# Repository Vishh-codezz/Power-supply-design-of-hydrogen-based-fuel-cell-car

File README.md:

# Power-supply-design-of-hydrogen-based-fuel-cell-car
I have developed nine power supply designs of on board battery and fuel cell battery. On board battery supply: 24V to 3.3V, 5V, 12V, dual 12V, dual 5V . Fuel cell supply: 48V to 3.3V, 5V, 12V, dual 5V, dual 12V.

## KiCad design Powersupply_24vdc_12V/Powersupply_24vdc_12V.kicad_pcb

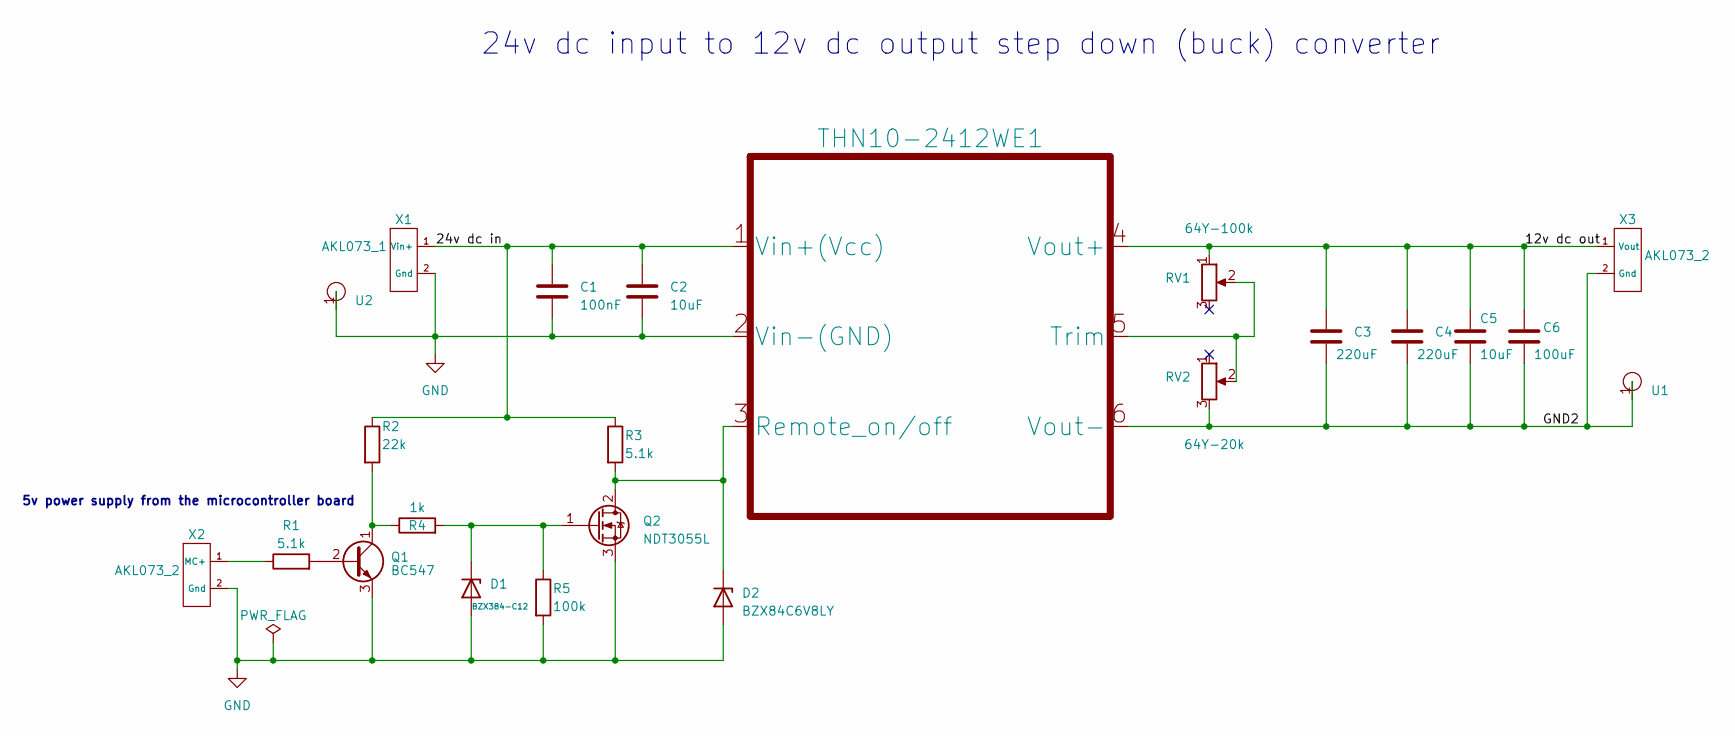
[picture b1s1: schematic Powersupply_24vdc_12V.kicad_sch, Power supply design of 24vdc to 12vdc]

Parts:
C1: 100nF; C_0603_1608Metric_Pad1.08x0.95mm_HandSolder
C2, C5: 10uF; C_1210_3225Metric_Pad1.33x2.70mm_HandSolder
C3, C4: 220uF
C6: 100uF; C_0603_1608Metric_Pad1.08x0.95mm_HandSolder
D1: BZX384-C12; BZX384_C12
D2: BZX84C6V8LY; BZX84C6V8
Q1: BC547; TO-92_Inline
Q2: NDT3055L; SOT-223-3_TabPin2
R1, R3: 5.1k; R_0603_1608Metric_Pad0.98x0.95mm_HandSolder
R2: 22k; R_0603_1608Metric_Pad0.98x0.95mm_HandSolder
R4: 1k; R_0603_1608Metric_Pad0.98x0.95mm_HandSolder
R5: 100k; R_1206_3216Metric_Pad1.30x1.75mm_HandSolder
RV1: 64Y-100k; Trim_potentiometer
RV2: 64Y-20k; 64Y-20k_potentiometer
THN10-2412WE1: Traco_THN-2412WE
U1, U2: Soldernail
X1: AKL073_1; 2pin_screwterminal
X2, X3: AKL073_2; 2pin_screwterminal

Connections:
/12v dc out: C3.1, C4.1, C5.1, C6.1, RV1.1, THN10-2412WE1.4 (Vout+), X3.1 (Vout); also elsewhere on the board
/24v dc in: C1.1, C2.1, R2.1, R3.1, THN10-2412WE1.1 (Vin+(Vcc)), X1.1 (Vin+); also elsewhere on the board
/GND2: C3.2, C4.2, C5.2, C6.2, RV2.3, THN10-2412WE1.6 (Vout-), U1.1, X3.2 (Gnd); also elsewhere on the board
GND: C1.2, C2.2, D1.2 (A), D2.2 (A), Q1.3 (E), Q2.3 (S), R5.2, THN10-2412WE1.2 (Vin-(GND)), U2.1, X1.2 (Gnd), X2.2 (Gnd); also elsewhere on the board
unnamed: D1.1 (K), Q2.1 (G), R4.2, R5.1
unnamed 5: D2.1 (K), Q2.2 (D), R3.2, THN10-2412WE1.3 (Remote_on/off); also elsewhere on the board
unnamed: Q1.2 (B), R1.2
unnamed: Q1.1 (C), R2.2, R4.1
unnamed 8: RV1.2, RV2.2, THN10-2412WE1.5 (Trim); also elsewhere on the board
unnamed: R1.1, X2.1 (MC+)

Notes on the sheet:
24v dc input to 12v dc output step down (buck) converter
5v power supply from the microcontroller board

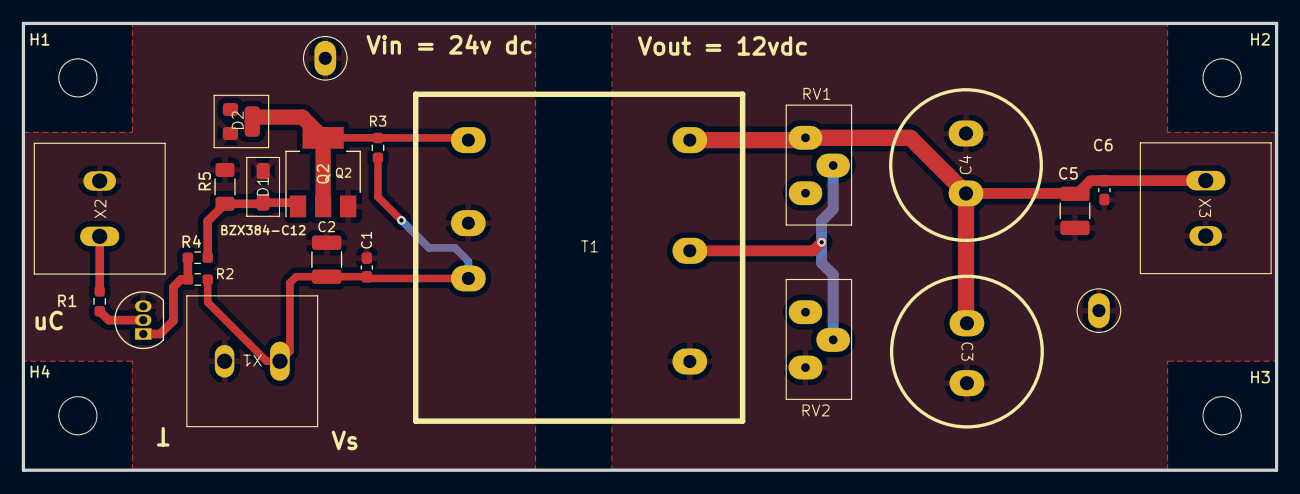
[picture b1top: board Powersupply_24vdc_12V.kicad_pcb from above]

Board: 2 copper layers, 115.0 x 41.0 mm, 27 parts (0 on the bottom side), 10 nets.

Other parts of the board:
H1, H2, H3, H4: MountingHole_3.5mm
T1: THN10-2412WE1; Traco_THN-2412WE

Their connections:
/12v dc out: T1.4 (Vout+); also elsewhere on the board
/24v dc in: T1.1 (Vin+(Vcc)); also elsewhere on the board
/GND2: T1.6 (Vout-); also elsewhere on the board
GND: T1.2 (Vin-(GND)); also elsewhere on the board
unnamed 5: T1.3 (Remote_on/off); also elsewhere on the board
unnamed 8: T1.5 (Trim); also elsewhere on the board

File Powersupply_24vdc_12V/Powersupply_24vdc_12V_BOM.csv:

Source:,C:\Kicad\Powersupply_12V\Powersupply_24vdc_12V\Powersupply_24vdc_12V.kicad_sch,,,,,,
Date:,6/11/2024 13:01,,,,,,
Tool:,Eeschema 7.0.1,,,,,,
Generator:,C:\Program Files\KiCad\7.0\bin\scripting\plugins/bom_csv_grouped_by_value_with_fp.py,,,,,,
Component Count:,23,,,,,,
Ref,Qnty,Value,Cmp name,Footprint,Description,Vendor,DNP
C1,1,100nF,C,Capacitor_SMD:C_0603_1608Metric_Pad1.08x0.95mm_HandSolder,Unpolarized capacitor,,
"C2, C5",2,10uF,C,Capacitor_SMD:C_1210_3225Metric_Pad1.33x2.70mm_HandSolder,Unpolarized capacitor,,
"C3, C4",2,220uF,C,220uf_capacitor:220uF,Unpolarized capacitor,,
C6,1,100uF,C,Capacitor_SMD:C_0603_1608Metric_Pad1.08x0.95mm_HandSolder,Unpolarized capacitor,,
D1,1,BZX384-C12,D_Zener,Zenerdiode_D1:BZX384_C12,Zener diode,,
D2,1,BZX84C6V8LY,D_Zener,Zenerdiode_D2:BZX84C6V8,Zener diode,,
Q1,1,BC547,BC547,Package_TO_SOT_THT:TO-92_Inline,"0.1A Ic, 45V Vce, Small Signal NPN Transistor, TO-92",,
Q2,1,NDT3055L,NDT3055L,Package_TO_SOT_SMD:SOT-223-3_TabPin2,"4A Id, 60V Vds, N-Channel Logic Level Enhancement Mode MOSFET, SOT-223",,
"R1, R3",2,5.1k,R,Resistor_SMD:R_0603_1608Metric_Pad0.98x0.95mm_HandSolder,Resistor,,
R2,1,22k,R,Resistor_SMD:R_0603_1608Metric_Pad0.98x0.95mm_HandSolder,Resistor,,
R4,1,1k,R,Resistor_SMD:R_0603_1608Metric_Pad0.98x0.95mm_HandSolder,Resistor,,
R5,1,100k,R,Resistor_SMD:R_1206_3216Metric_Pad1.30x1.75mm_HandSolder,Resistor,,
RV1,1,64Y-100k,R_Potentiometer,64Y-100k:Trim_potentiometer,Potentiometer,,
RV2,1,64Y-20k,R_Potentiometer,64Y-20k:64Y-20k_potentiometer,Potentiometer,,
THN10-2412WE1,1,~,THN10-2412WE,THN-2412WE:Traco_THN-2412WE,,,
"U1, U2",2,~,soldernail,soldernail-RTML:Soldernail,,,
X1,1,AKL073_1,input_1,AKL073_2:2pin_screwterminal,,,
"X2, X3",2,AKL073_2,input_2,AKL073_2:2pin_screwterminal,,,

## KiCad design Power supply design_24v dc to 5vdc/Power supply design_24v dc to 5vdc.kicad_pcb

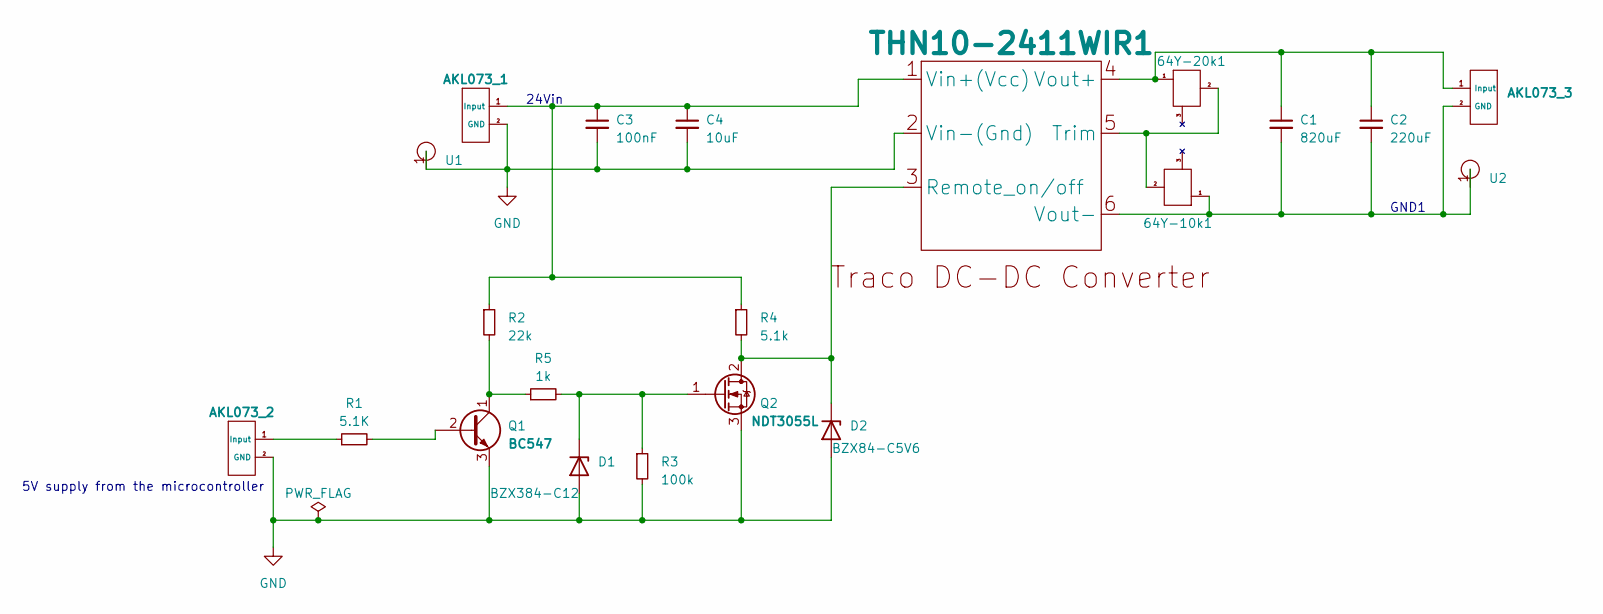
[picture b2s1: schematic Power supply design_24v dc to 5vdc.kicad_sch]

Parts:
64Y-10k1, 64Y-20k1: 64Y-100k
AKL073_1, AKL073_2, AKL073_3: Screw-terminal
C1: 820uF; 820uF_63V
C2: 220uF
C3: 100nF; C_1210_3225Metric_Pad1.33x2.70mm_HandSolder
C4: 10uF; C_1210_3225Metric_Pad1.33x2.70mm_HandSolder
D1: BZX384-C12; Zenerdiode_5.6V
D2: BZX84-C5V6
Q1: BC547; TO-92_Inline
Q2: NDT3055L; SOT-223-3_TabPin2
R1: 5.1K; R_0603_1608Metric_Pad0.98x0.95mm_HandSolder
R2: 22k; R_0603_1608Metric_Pad0.98x0.95mm_HandSolder
R3: 100k; R_1206_3216Metric_Pad1.30x1.75mm_HandSolder
R4: 5.1k; R_0603_1608Metric_Pad0.98x0.95mm_HandSolder
R5: 1k; R_0603_1608Metric_Pad0.98x0.95mm_HandSolder
THN10-2411WIR1: THN2411WIR
U1, U2: Soldernail

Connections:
GND: AKL073_1.2 (GND), AKL073_2.2 (GND), C3.2, C4.2, D1.2 (A), D2.2 (A), Q1.3 (E), Q2.3 (S), R3.2, THN10-2411WIR1.2 (Vin-(Gnd)), U1.1
unnamed: AKL073_1.1 (Input), C3.1, C4.1, R2.1, R4.1, THN10-2411WIR1.1 (Vin+(Vcc))
unnamed: AKL073_2.1 (Input), R1.1
unnamed: 64Y-10k1.1, AKL073_3.2 (GND), C1.2, C2.2, THN10-2411WIR1.6 (Vout-), U2.1
unnamed: 64Y-20k1.1, AKL073_3.1 (Input), C1.1, C2.1, THN10-2411WIR1.4 (Vout+)
unnamed: D1.1 (K), Q2.1 (G), R3.1, R5.2
unnamed: D2.1 (K), Q2.2 (D), R4.2, THN10-2411WIR1.3 (Remote_on/off)
unnamed: Q1.2 (B), R1.2
unnamed: Q1.1 (C), R2.2, R5.1
unnamed: 64Y-10k1.2, 64Y-20k1.2, THN10-2411WIR1.5 (Trim)

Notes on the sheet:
5V supply from the microcontroller
GND1
24Vin

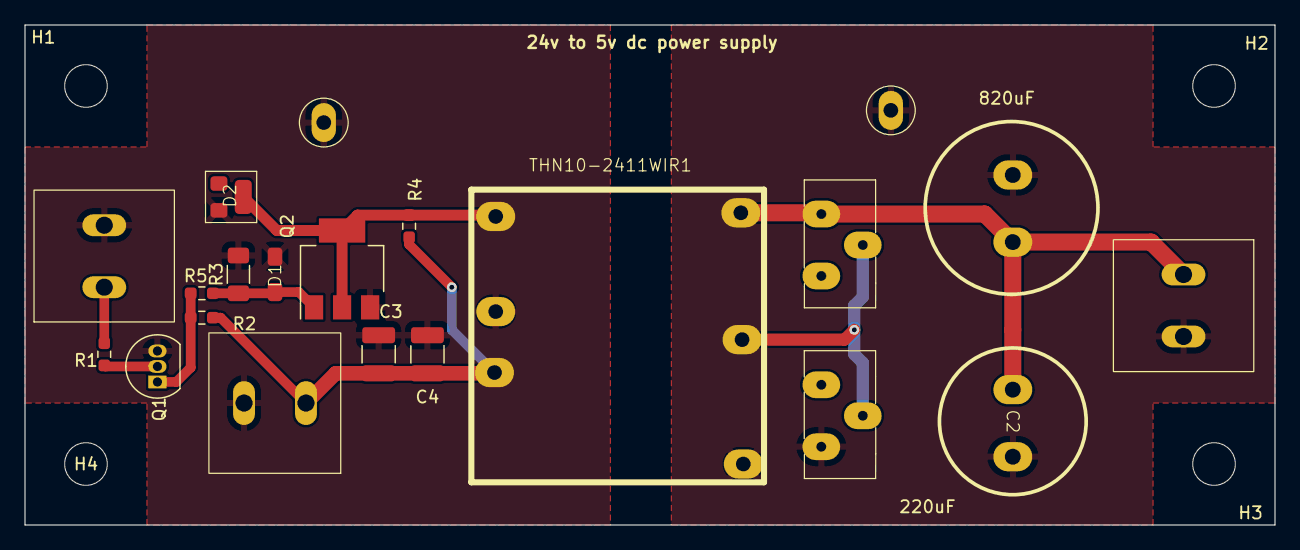
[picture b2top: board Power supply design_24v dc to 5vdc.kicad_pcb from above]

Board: 2 copper layers, 102.5 x 41.0 mm, 25 parts (0 on the bottom side), 10 nets.

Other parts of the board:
H1, H2, H3, H4: MountingHole_3.5mm

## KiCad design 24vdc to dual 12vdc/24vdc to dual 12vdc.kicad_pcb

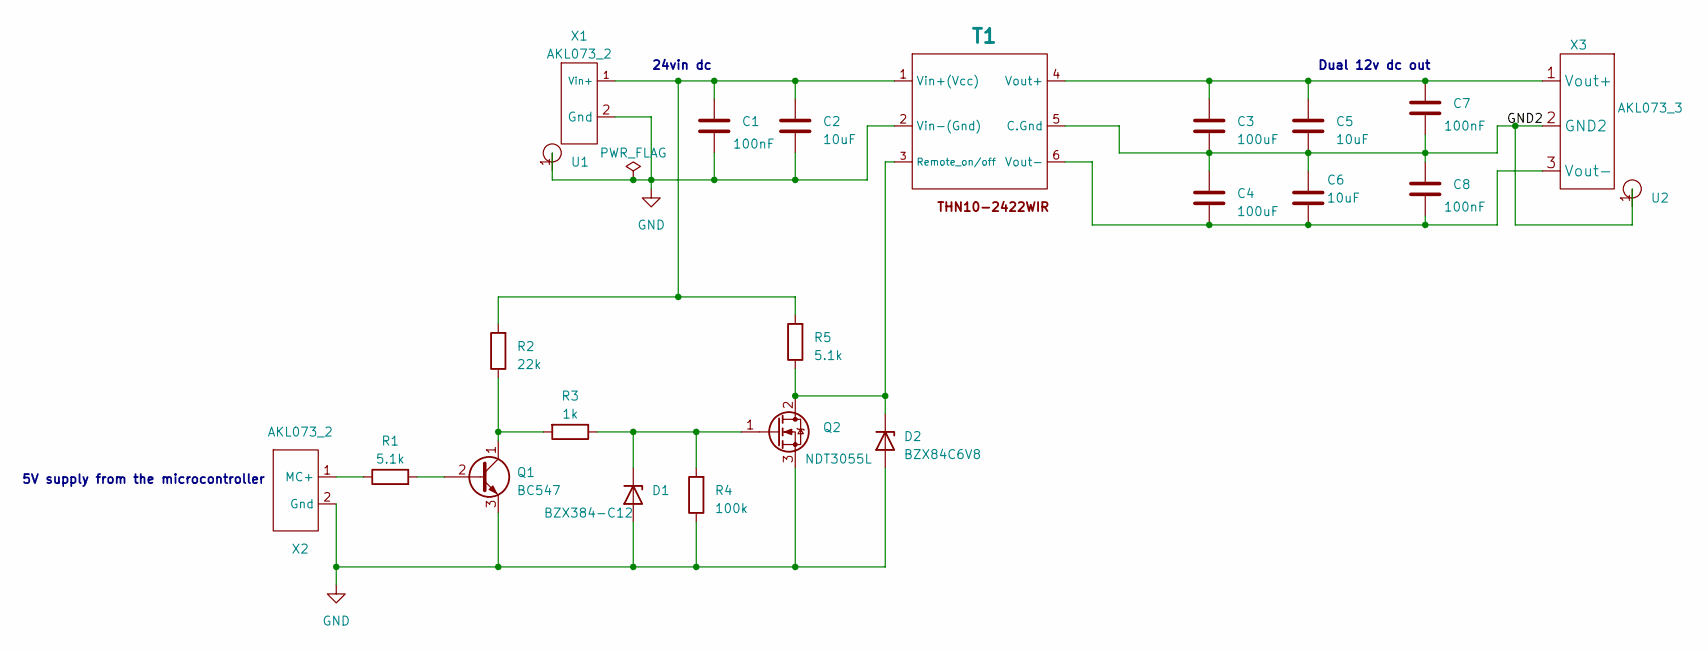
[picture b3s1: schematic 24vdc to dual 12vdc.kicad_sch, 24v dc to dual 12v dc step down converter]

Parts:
C1, C7, C8: 100nF; C_0603_1608Metric_Pad1.08x0.95mm_HandSolder
C2, C5, C6: 10uF; C_1210_3225Metric_Pad1.33x2.70mm_HandSolder
C3, C4: 100uF; Cout_100uf
D1: BZX384-C12
D2: BZX84C6V8; BZY84C6V8
Q1: BC547; TO-92_Inline
Q2: NDT3055L; SOT-223-3_TabPin2
R1, R5: 5.1k; R_0603_1608Metric_Pad0.98x0.95mm_HandSolder
R2: 22k; R_0603_1608Metric_Pad0.98x0.95mm_HandSolder
R3: 1k; R_0603_1608Metric_Pad0.98x0.95mm_HandSolder
R4: 100k; R_1206_3216Metric_Pad1.30x1.75mm_HandSolder
T1: Traco_THN10-2422WIR
U1, U2: Soldernail
X1, X2: AKL073_2
X3: AKL073_3

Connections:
/GND2: C3.2, C4.1, C5.2, C6.1, C7.2, C8.1, T1.5 (C.Gnd), U2.1, X3.2 (GND2)
GND: C1.2, C2.2, D1.2 (A), D2.2 (A), Q1.3 (E), Q2.3 (S), R4.1, T1.2 (Vin-(Gnd)), U1.1, X1.2 (Gnd), X2.2 (Gnd)
unnamed: D1.1 (K), Q2.1 (G), R3.1, R4.2
unnamed: D2.1 (K), Q2.2 (D), R5.1, T1.3 (Remote_on/off)
unnamed: Q1.2 (B), R1.2
unnamed: Q1.1 (C), R2.1, R3.2
unnamed: C1.1, C2.1, R2.2, R5.2, T1.1 (Vin+(Vcc)), X1.1 (Vin+)
unnamed: C3.1, C5.1, C7.1, T1.4 (Vout+), X3.1 (Vout+)
unnamed: C4.2, C6.2, C8.2, T1.6 (Vout-), X3.3 (Vout-)
unnamed: R1.1, X2.1 (MC+)

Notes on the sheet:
Dual 12v dc out
5V supply from the microcontroller
24vin dc

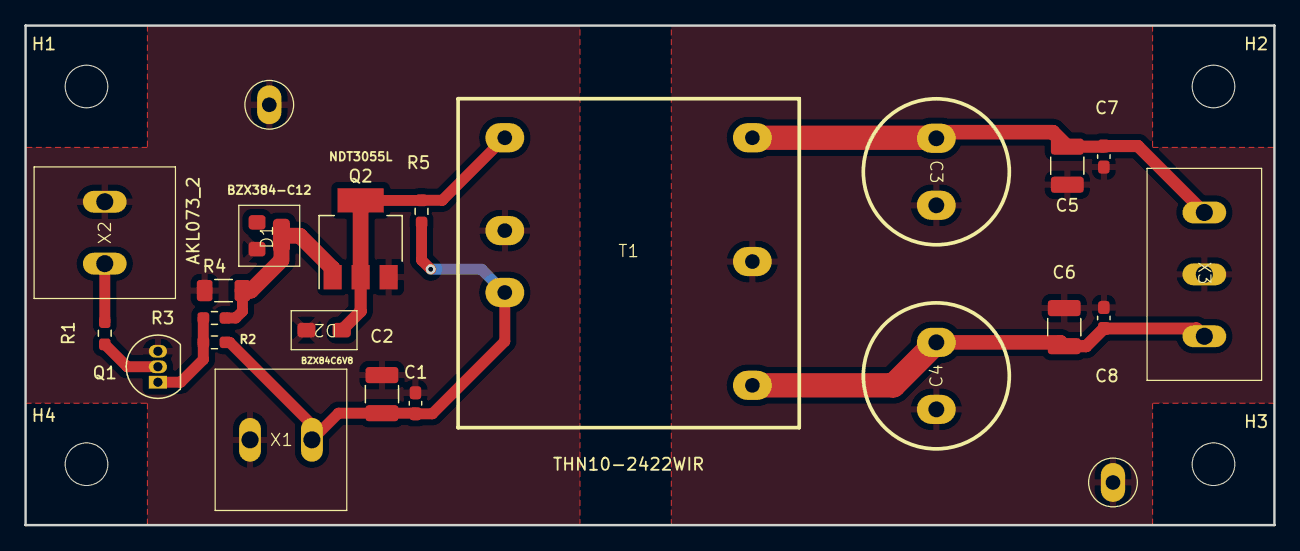
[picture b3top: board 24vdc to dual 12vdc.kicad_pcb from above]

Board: 2 copper layers, 102.5 x 41.0 mm, 27 parts (0 on the bottom side), 10 nets.

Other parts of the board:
H1, H2, H3, H4: MountingHole_3.5mm

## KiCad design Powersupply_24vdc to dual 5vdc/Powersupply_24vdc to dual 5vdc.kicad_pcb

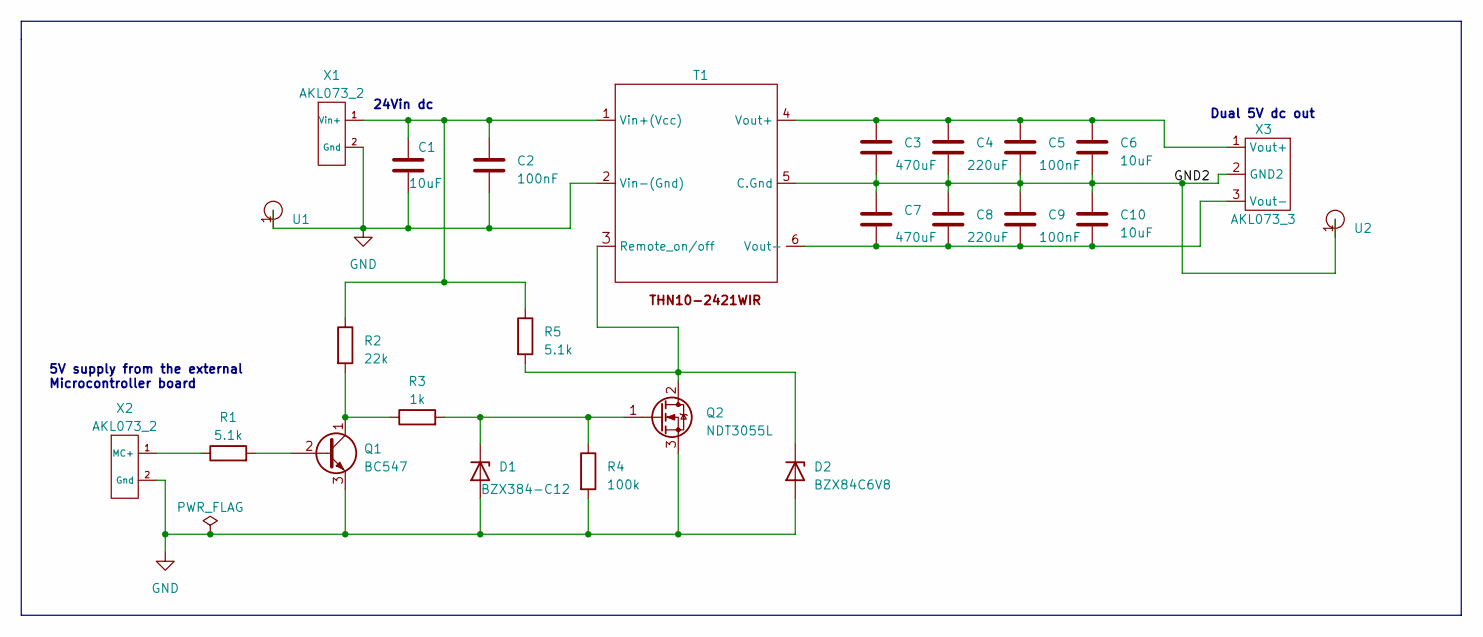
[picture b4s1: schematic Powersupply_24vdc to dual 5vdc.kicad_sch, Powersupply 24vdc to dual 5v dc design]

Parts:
C1, C6, C10: 10uF; C_1210_3225Metric_Pad1.33x2.70mm_HandSolder
C2, C5, C9: 100nF; C_0603_1608Metric_Pad1.08x0.95mm_HandSolder
C3, C7: 470uF; 470uf
C4, C8: 220uF
D1: BZX384-C12
D2: BZX84C6V8; BZY84C6V8
Q1: BC547; TO-92_Inline
Q2: NDT3055L; SOT-223-3_TabPin2
R1, R5: 5.1k; R_0603_1608Metric_Pad0.98x0.95mm_HandSolder
R2: 22k; R_0603_1608Metric_Pad0.98x0.95mm_HandSolder
R3: 1k; R_0603_1608Metric_Pad0.98x0.95mm_HandSolder
R4: 100k; R_1210_3225Metric_Pad1.30x2.65mm_HandSolder
T1: THN10-2422WIR
U1, U2: Soldernail
X1, X2: AKL073_2
X3: AKL073_3

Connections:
/GND2: C3.2, C4.2, C5.2, C6.2, C7.1, C8.1, C9.1, C10.1, T1.5 (C.Gnd), U2.1, X3.2 (GND2)
GND: C1.2, C2.2, D1.2 (A), D2.2 (A), Q1.3 (E), Q2.3 (S), R4.2, T1.2 (Vin-(Gnd)), U1.1, X1.2 (Gnd), X2.2 (Gnd)
unnamed: D1.1 (K), Q2.1 (G), R3.2, R4.1
unnamed: D2.1 (K), Q2.2 (D), R5.2, T1.3 (Remote_on/off)
unnamed: Q1.2 (B), R1.2
unnamed: Q1.1 (C), R2.2, R3.1
unnamed: C1.1, C2.1, R2.1, R5.1, T1.1 (Vin+(Vcc)), X1.1 (Vin+)
unnamed: C3.1, C4.1, C5.1, C6.1, T1.4 (Vout+), X3.1 (Vout+)
unnamed: C7.2, C8.2, C9.2, C10.2, T1.6 (Vout-), X3.3 (Vout-)
unnamed: R1.1, X2.1 (MC+)

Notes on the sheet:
5V supply from the external Microcontroller board
Dual 5V dc out
24Vin dc

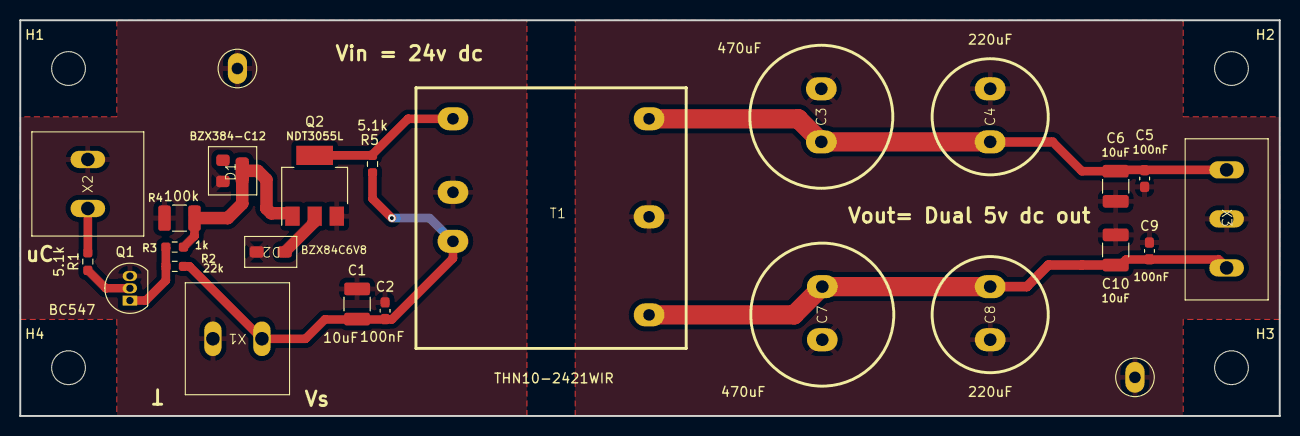
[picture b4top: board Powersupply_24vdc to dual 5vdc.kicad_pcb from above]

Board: 2 copper layers, 130.5 x 41.0 mm, 29 parts (0 on the bottom side), 10 nets.

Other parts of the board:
H1, H2, H3, H4: MountingHole_3.5mm

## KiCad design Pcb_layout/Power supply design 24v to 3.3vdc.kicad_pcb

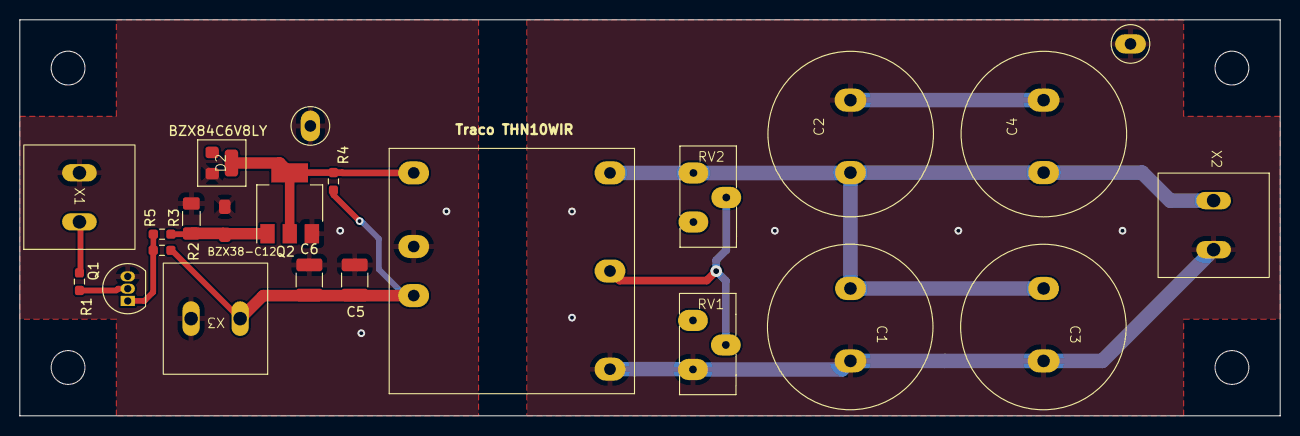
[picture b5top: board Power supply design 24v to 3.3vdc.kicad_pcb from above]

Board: 2 copper layers, 130.5 x 41.0 mm, 23 parts (0 on the bottom side), 10 nets.

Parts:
C1, C2, C3, C4: 680uF; 680uF_Capacitance_Footprint
C5: 100nF; C_1210_3225Metric_Pad1.33x2.70mm_HandSolder
C6: 10uF; C_1210_3225Metric_Pad1.33x2.70mm_HandSolder
D1: BZX384-C12; Zenerdiode
D2: BZX84C6V8LY; Zenerdiode_6.8V
Q1: BC547; TO-92_Inline
Q2: NDT3055L; SOT-223-3_TabPin2
R1, R4: 5.1K; R_0603_1608Metric_Pad0.98x0.95mm_HandSolder
R2: 22k; R_0603_1608Metric_Pad0.98x0.95mm_HandSolder
R3: 100k; R_1206_3216Metric_Pad1.30x1.75mm_HandSolder
R5: 1K; R_0603_1608Metric_Pad0.98x0.95mm_HandSolder
RV1, RV2: R_Potentiometer; 64Y-100k
THN10WIR1: Traco_dc_dc_converter_footprint
U1, U2: Soldernail
X1, X3: AKL073-2; Screw-terminal
X2: AKL073_1; Screw-terminal

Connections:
/GND2: C1.2, C2.2, C3.2, C4.2, RV1.3, THN10WIR1.6 (Vout-), U1.1, X2.2 (GND)
GND: C5.2, C6.2, D1.2 (A), D2.2 (A), Q1.3 (E), Q2.3 (S), R3.2, THN10WIR1.2 (Vin-(Gnd)), U2.1, X1.2 (GND), X3.2 (GND)
unnamed: D1.1 (K), Q2.1 (G), R3.1, R5.2
unnamed: D2.1 (K), Q2.2 (D), R4.2, THN10WIR1.3 (Remote_on/off)
unnamed: Q1.2 (B), R1.2
unnamed: Q1.1 (C), R2.2, R5.1
unnamed: RV1.2, RV2.2, THN10WIR1.5 (Trim)
unnamed: C5.1, C6.1, R2.1, R4.1, THN10WIR1.1 (Vin+(Vcc)), X3.1 (Input)
unnamed: C1.1, C2.1, C3.1, C4.1, RV2.1, THN10WIR1.4 (Vout+), X2.1 (Output)
unnamed: R1.1, X1.1 (Input)

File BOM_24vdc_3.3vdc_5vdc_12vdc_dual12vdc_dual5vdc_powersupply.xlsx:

Reference | Value | Footprint | Datasheet | Qty | Part number | Price | Manufacturer | Distributor
C1-C4 | 680uF | 680uF_Capacitance_Footprint:680uF_Capacitance_Footprint | https://cdn-reichelt.de/documents/datenblatt/B300/ELXZ_DS.pdf | 4 | RAD FC 680/100 | 10.199999999999999 | Panasonic | Reichelt
C5 | 100nF | Capacitor_SMD:C_1210_3225Metric_Pad1.33x2.70mm_HandSolder | https://www.reichelt.de/de/en/multi-layer-ceramic-capacitor-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 | 2 | KEM X7R1210 100N | 0.54 | Kemet | Reichelt
C6 | 10uF | Capacitor_SMD:C_1210_3225Metric_Pad1.33x2.70mm_HandSolder | https://www.reichelt.de/de/en/e-cap-radial-10-uf-63-v-2000-h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 | 1 | M-A 10U 63 | 0.09 | Panasonic | Reichelt
D1 | BZX384-C12 | BZX384-C12:Zenerdiode | https://www.mouser.de/datasheet/2/916/BZX384_SER-2938013.pdf | 1 | 771-BZX384-C12115 | 0.18 | Nexperia | Mouser
D2 | BZX84C6V8LY | BZX384C6BV8:Zenerdiode_6.8V | https://assets.nexperia.com/documents/data-sheet/BZX84_SER.pdf | 1 | 771-BZX84-C6V8-T/R | 0.15 | Nexperia | Mouser
Q1 | BC547 | Package_TO_SOT_THT:TO-92_Inline | https://www.onsemi.com/pub/Collateral/BC550-D.pdf | 1 | 512-BC547B | 0.42 | Onsemi | Mouser
Q2 | NDT3055L | Package_TO_SOT_SMD:SOT-223-3_TabPin2 | https://www.onsemi.com/pdf/datasheet/ndt3055l-d.pdf | 1 | 512-NDT3055L | 0.93 | Onsemi | Mouser
R1, R4 | 5.1K | Resistor_SMD:R_0603_1608Metric_Pad0.98x0.95mm_HandSolder | https://www.mouser.de/ProductDetail/Vishay-Dale/CRCW06035K10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 | 2 | 71-CRCW06035K10FKEC | 0.18 | Vishay | Mouser
R2 | 22k | Resistor_SMD:R_0603_1608Metric_Pad0.98x0.95mm_HandSolder | https://www.mouser.de/ProductDetail/Vishay-Dale/CRCW060322K0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 | 1 | 71-CRCW060322K0FKEBC | 0.09 | Vishay | Mouser
R3 | 100k | Resistor_SMD:R_1206_3216Metric_Pad1.30x1.75mm_HandSolder | https://www.mouser.de/ProductDetail/Vishay/RCV1206100KFKEAAT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 | 1 | 71-RCV1206100KFKEAAT | 0.03 | Vishay | Mouser
R5 | 1K | Resistor_SMD:R_0603_1608Metric_Pad0.98x0.95mm_HandSolder | https://www.mouser.de/ProductDetail/Vishay-Dale/CRCW06031K00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 | 1 | 71-CRCW06031K00FKEAH | 0.13 | Vishay | Mouser
RV1, RV2 | R_Potentiometer | Potentiometer:64Y-100k | https://www.vishay.com/docs/57028/64.pdf | 2 | 64Y-10K,64Y-100k | 1.70€,1.35€ |  | Reichelt
THN10WIR1 |  | Traco_dc_dc:Traco_dc_dc_converter_footprint | https://www.tracopower.com/sites/default/files/products/data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 | 1 | 495-THN10-2410WE | 36.96 | Traco power | Mouser
U1, U2 |  | soldernail-RTML:Soldernail |  | 2
X1, X3 | AKL073-2 | AKL073_02:Screw-terminal | https://www.phoenixcontact.com/en-us/products/printed-circui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 | 2 | 651-1729128 | 1.44 | Phoenix contact | Mouser
X2 | AKL073_1 | AKL073_02:Screw-terminal | https://www.phoenixcontact.com/en-us/products/printed-circui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 | 1 | 651-1729128 | 0.72 | Phoenix contact | Mouser
